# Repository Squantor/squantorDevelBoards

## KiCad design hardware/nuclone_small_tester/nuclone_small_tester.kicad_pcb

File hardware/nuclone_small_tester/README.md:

# Small nuclone peripheral tester
Small nuclone expansion board used for peripheral testing of nuclone boards
## TODO's
Still some things need to be done:
* schematic entry (WIP)
* PCB layout (TODO)
* Review with one night in between (TODO)
* Produce at [OSHPARK](https://oshpark.com/) (TODO)
* Assemble (TODO)
* Test & characterise (TODO)
* update Readme.md with pictures and BOM (TODO)

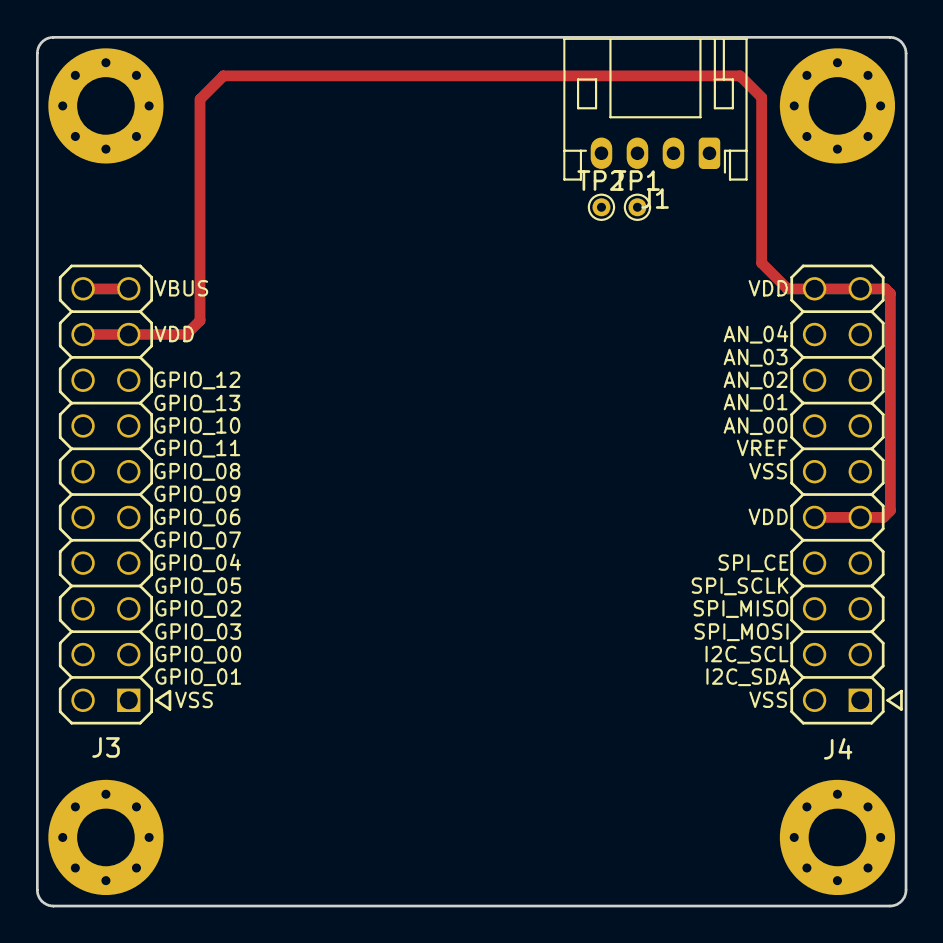
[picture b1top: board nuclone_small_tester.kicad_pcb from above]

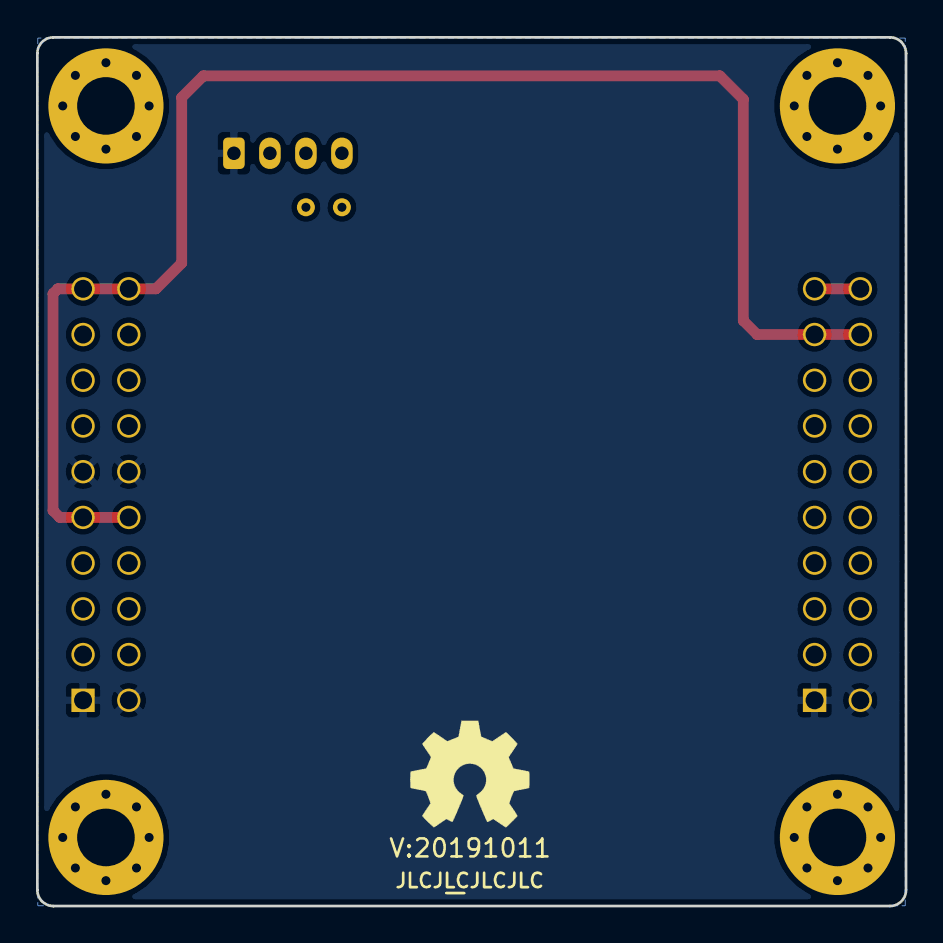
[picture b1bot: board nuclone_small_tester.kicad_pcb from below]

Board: 2 copper layers, 48.3 x 48.3 mm, 12 parts (3 on the bottom side), 5 nets.

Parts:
H1, H2, H3, H4: MountingHole; MountingHole_3.2mm_M3_Pad_Via
J1: DevBoardUartInput; JST_PH_S4B-PH-K_1x04_P2.00mm_Horizontal
J3: nuclone_small_exp_gpio
J4: nuclone_small_exp_bus_analog
N1: OHWLOGO; OSHW-Symbol_6.7x6mm_SilkScreen
N2: 20191011; Label_version
N3: JLCJLCJLCJLC; Label_Generic
TP1, TP2: testpad; TestPoint_THTPad_D1.0mm_Drill0.5mm

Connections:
/UART_RX: J1.3, TP1.1
/UART_TX: J1.4, TP2.1
/VBUS: J1.2, J3.19, J3.20
/VDD: J3.17, J3.18, J4.9, J4.10, J4.19, J4.20
/VSS: J1.1, J3.1, J3.2, J4.1, J4.2, J4.11, J4.12

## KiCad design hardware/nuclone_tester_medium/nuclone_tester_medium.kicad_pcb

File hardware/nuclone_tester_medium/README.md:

# Nuclone tester for medium sized boards
Test jig for the Medium sized nuclone boards.
## TODO's
Still some things need to be done:
* schematic entry (WIP)
* PCB layout (WIP)
* Review with one night in between (TODO)
* Produce at [JLCPCB](https://jlcpcb.com/) (TODO)
* Assemble (TODO)
* Test & characterise (TODO)
* update Readme.md with pictures and BOM (TODO)

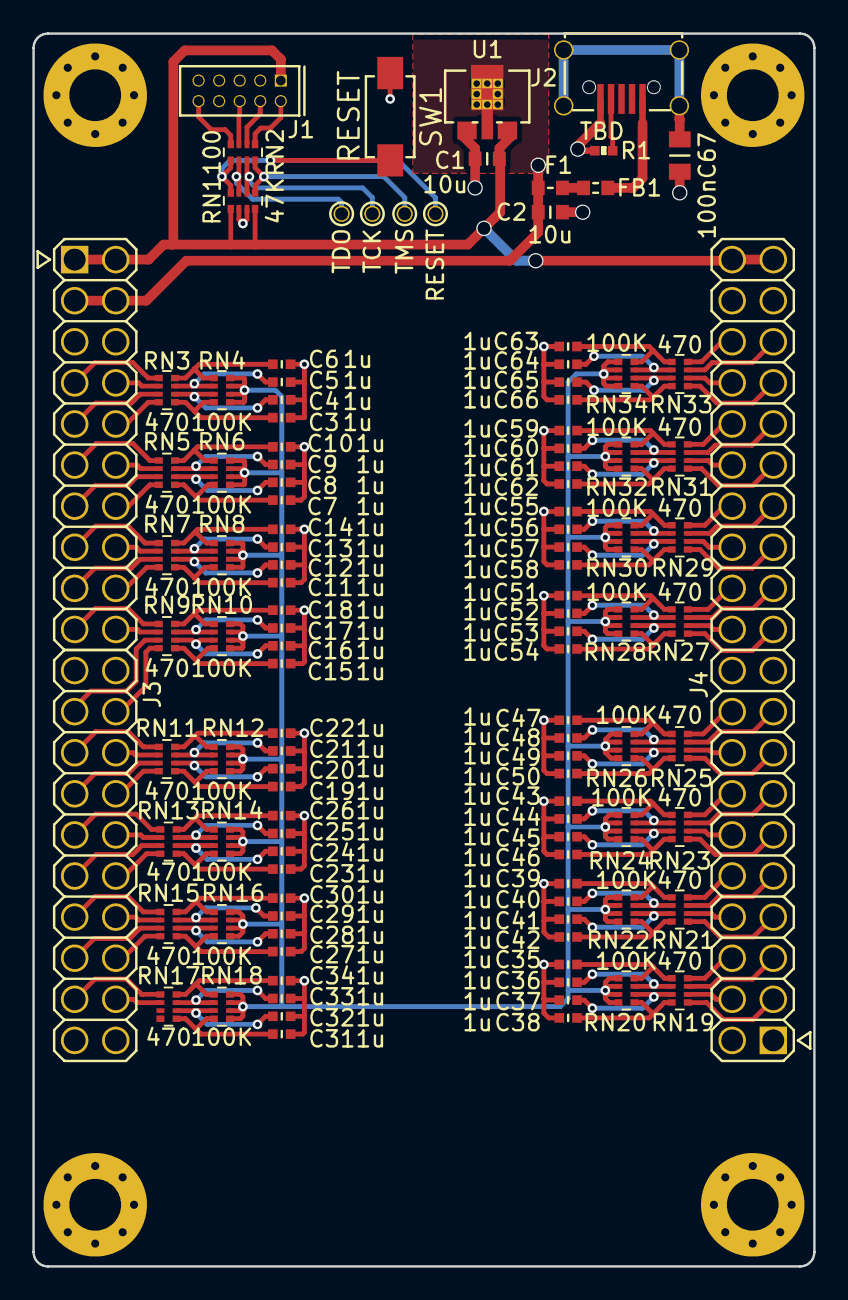
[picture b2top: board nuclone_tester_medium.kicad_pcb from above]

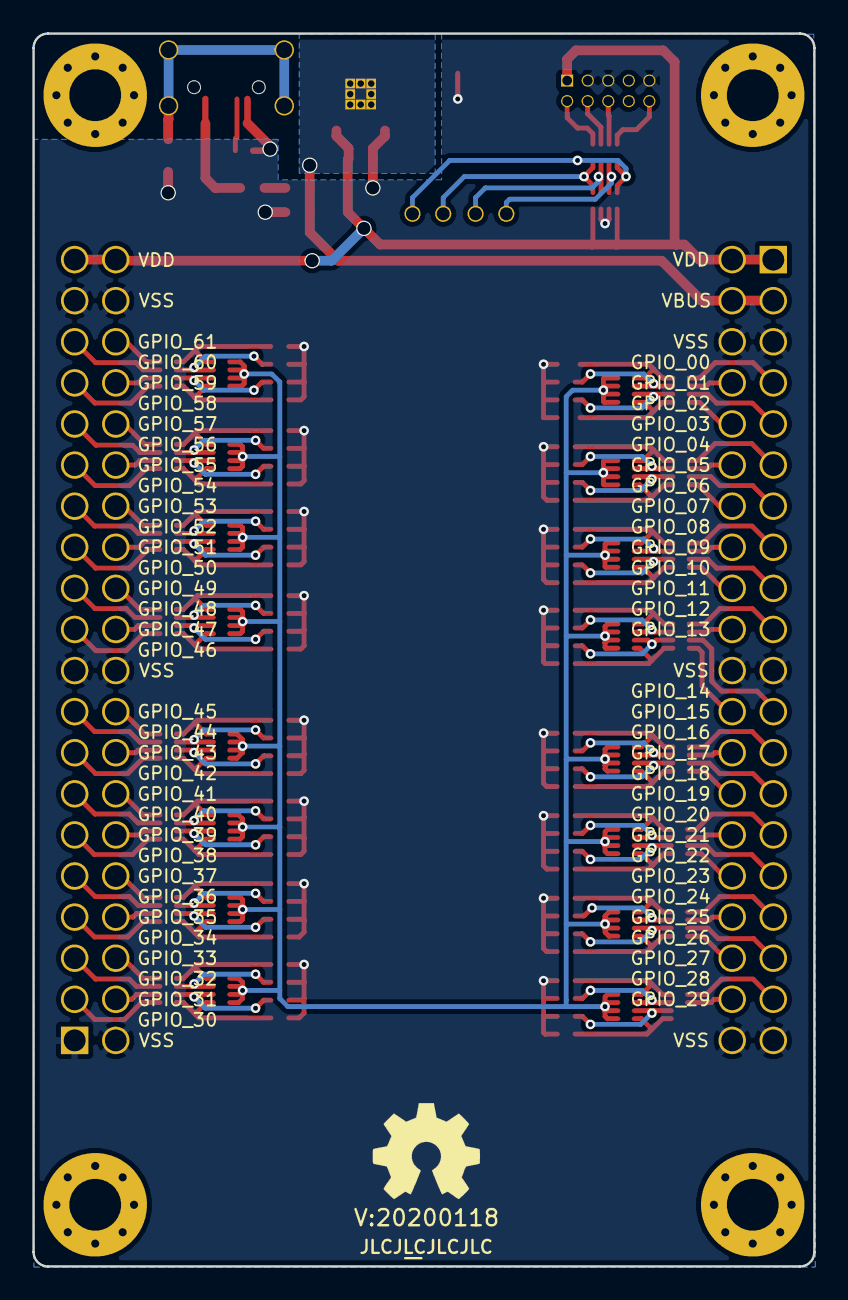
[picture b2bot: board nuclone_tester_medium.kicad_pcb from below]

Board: 2 copper layers, 48.3 x 76.2 mm, 121 parts (3 on the bottom side), 142 nets.

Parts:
C1, C2: 10u; C_0603
C3, C4, C5, C6, C7, C8, C9, C10, C11, C12, C13, C14, C15, C16, C17, C18, C19, C20, C21, C22, C23, C24, C25, C26, C27, C28, C29, C30, C31, C32, C33, C34, C35, C36, C37, C38, C39, C40, C41, C42, C43, C44, C45, C46, C47, C48, C49, C50, C51, C52, C53, C54, C55, C56, C57, C58, C59, C60, C61, C62, C63, C64, C65, C66: 1u; C_0402
C67: 100n; C_0805
F1: 0.5A; F_0603_hand
FB1: 100; L_0603
H1, H2, H3, H4: MountingHole; MountingHole_3.2mm_M3_Pad_Via
J1: JTAG_2X05; Header-0127-2X05-H006
J2: USB-ID; USB-muB-SMD_TH
J3: nuclone_small_left; nuclone_medium_left_1_35mm
J4: nuclone_small_right; nuclone_medium_right_1_35mm
N1: OHWLOGO; OSHW-Symbol_6.7x6mm_SilkScreen
N2: 20200118; Label_version
N3: JLCJLCJLCJLC; Label_Generic
R1: TBD; R_0402_hand
RN1: 47K; R_Array_Convex_4x0402
RN2: 100; R_Array_Convex_4x0402
RN3, RN5, RN7, RN9, RN11, RN13, RN15, RN17, RN19, RN21, RN23, RN25, RN27, RN29, RN31, RN33: 470; R_Array_Convex_4x0402
RN4, RN6, RN8, RN10, RN12, RN14, RN16, RN18, RN20, RN22, RN24, RN26, RN28, RN30, RN32, RN34: 100K; R_Array_Convex_4x0402
SW1: RESET; DTSM3
TP1: TMS; TestPoint_Hole_D0.8mm
TP2: TCK; TestPoint_Hole_D0.8mm
TP3: TDO; TestPoint_Hole_D0.8mm
TP4: RESET; TestPoint_Hole_D0.8mm
U1: MCP1702-MB; SOT89-SOT23-Dual-NXP

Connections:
/GPIO_00: J3.7, RN3.1
/GPIO_01: J3.8, RN3.2
/GPIO_02: J3.9, RN3.3
/GPIO_03: J3.10, RN3.4
/GPIO_04: J3.11, RN5.1
/GPIO_05: J3.12, RN5.2
/GPIO_06: J3.13, RN5.3
/GPIO_07: J3.14, RN5.4
/GPIO_08: J3.15, RN7.1
/GPIO_09: J3.16, RN7.2
/GPIO_10: J3.17, RN7.3
/GPIO_11: J3.18, RN7.4
/GPIO_12: J3.19, RN9.1
/GPIO_13: J3.20, RN9.2
/GPIO_14: J3.23, RN9.3
/GPIO_15: J3.24, RN9.4
/GPIO_16: J3.25, RN11.1
/GPIO_17: J3.26, RN11.2
/GPIO_18: J3.27, RN11.3
/GPIO_19: J3.28, RN11.4
/GPIO_20: J3.29, RN13.1
/GPIO_21: J3.30, RN13.2
/GPIO_22: J3.31, RN13.3
/GPIO_23: J3.32, RN13.4
/GPIO_24: J3.33, RN15.1
/GPIO_25: J3.34, RN15.2
/GPIO_26: J3.35, RN15.3
/GPIO_27: J3.36, RN15.4
/GPIO_28: J3.37, RN17.1
/GPIO_29: J3.38, RN17.2
/GPIO_30: J4.3, RN19.1
/GPIO_31: J4.4, RN19.2
/GPIO_32: J4.5, RN19.3
/GPIO_33: J4.6, RN19.4
/GPIO_34: J4.7, RN21.1
/GPIO_35: J4.8, RN21.2
/GPIO_36: J4.9, RN21.3
/GPIO_37: J4.10, RN21.4
/GPIO_38: J4.11, RN23.1
/GPIO_39: J4.12, RN23.2
/GPIO_40: J4.13, RN23.3
/GPIO_41: J4.14, RN23.4
/GPIO_42: J4.15, RN25.1
/GPIO_43: J4.16, RN25.2
/GPIO_44: J4.17, RN25.3
/GPIO_45: J4.18, RN25.4
/GPIO_46: J4.21, RN27.1
/GPIO_47: J4.22, RN27.2
/GPIO_48: J4.23, RN27.3
/GPIO_49: J4.24, RN27.4
/GPIO_50: J4.25, RN29.1
/GPIO_51: J4.26, RN29.2
/GPIO_52: J4.27, RN29.3
/GPIO_53: J4.28, RN29.4
/GPIO_54: J4.29, RN31.1
/GPIO_55: J4.30, RN31.2
/GPIO_56: J4.31, RN31.3
/GPIO_57: J4.32, RN31.4
/GPIO_58: J4.33, RN33.1
/GPIO_59: J4.34, RN33.2
/GPIO_60: J4.35, RN33.3
/GPIO_61: J4.36, RN33.4
/PIO0_2_MCU: RN1.5, RN2.8, TP1.1
/PIO0_3_MCU: RN1.6, RN2.7, TP2.1
/PIO0_5_MCU: RN1.8, RN2.5, SW1.2, TP4.1
/SWO_TDO: RN1.7, RN2.6, TP3.1
/Stimulus: RN4.5, RN4.6, RN4.7, RN4.8, RN6.5, RN6.6, RN6.7, RN6.8, RN8.5, RN8.6, RN8.7, RN8.8, RN10.5, RN10.6, RN10.7, RN10.8, RN12.5, RN12.6, RN12.7, RN12.8, RN14.5, RN14.6, RN14.7, RN14.8, RN16.5, RN16.6, RN16.7, RN16.8, RN18.5, RN18.6, RN18.7, RN18.8, RN20.5, RN20.6, RN20.7, RN20.8, RN22.5, RN22.6, RN22.7, RN22.8, RN24.5, RN24.6, RN24.7, RN24.8, RN26.5, RN26.6, RN26.7, RN26.8, RN28.5, RN28.6, RN28.7, RN28.8, RN30.5, RN30.6, RN30.7, RN30.8, RN32.5, RN32.6, RN32.7, RN32.8, RN34.5, RN34.6, RN34.7, RN34.8
/VBUS: C2.2, F1.1, J3.3, J3.4, U1.2
/VDD: C1.1, J1.1, J3.1, J3.2, J4.39, J4.40, RN1.1, RN1.4, U1.3
/VSS: C1.2, C2.1, C3.2, C4.2, C5.2, C6.2, C7.2, C8.2, C9.2, C10.2, C11.2, C12.2, C13.2, C14.2, C15.2, C16.2, C17.2, C18.2, C19.2, C20.2, C21.2, C22.2, C23.2, C24.2, C25.2, C26.2, C27.2, C28.2, C29.2, C30.2, C31.2, C32.2, C33.2, C34.2, C35.2, C36.2, C37.2, C38.2, C39.2, C40.2, C41.2, C42.2, C43.2, C44.2, C45.2, C46.2, C47.2, C48.2, C49.2, C50.2, C51.2, C52.2, C53.2, C54.2, C55.2, C56.2, C57.2, C58.2, C59.2, C60.2, C61.2, C62.2, C63.2, C64.2, C65.2, C66.2, C67.2, J1.3, J1.5, J1.9, J2.5, J3.5, J3.6, J3.21, J3.22, J3.39, J3.40, J4.1, J4.2, J4.19, J4.20, J4.37, J4.38, R1.1, RN1.2, RN1.3, SW1.1, U1.1
unnamed: C3.1, RN3.5, RN4.4
unnamed: C4.1, RN3.6, RN4.3
unnamed: C5.1, RN3.7, RN4.2
unnamed: C6.1, RN3.8, RN4.1
unnamed: C7.1, RN5.5, RN6.4
unnamed: C8.1, RN5.6, RN6.3
unnamed: C9.1, RN5.7, RN6.2
unnamed: C10.1, RN5.8, RN6.1
unnamed: C11.1, RN7.5, RN8.4
unnamed: C12.1, RN7.6, RN8.3
unnamed: C13.1, RN7.7, RN8.2
unnamed: C14.1, RN7.8, RN8.1
unnamed: C15.1, RN9.5, RN10.4
unnamed: C16.1, RN9.6, RN10.3
unnamed: C17.1, RN9.7, RN10.2
unnamed: C18.1, RN9.8, RN10.1
unnamed: C19.1, RN11.5, RN12.4
unnamed: C20.1, RN11.6, RN12.3
unnamed: C21.1, RN11.7, RN12.2
unnamed: C22.1, RN11.8, RN12.1
unnamed: C23.1, RN13.5, RN14.4
unnamed: C24.1, RN13.6, RN14.3
unnamed: C25.1, RN13.7, RN14.2
unnamed: C26.1, RN13.8, RN14.1
unnamed: C27.1, RN15.5, RN16.4
unnamed: C28.1, RN15.6, RN16.3
unnamed: C29.1, RN15.7, RN16.2
unnamed: C30.1, RN15.8, RN16.1
unnamed: C31.1, RN17.5, RN18.4
unnamed: C32.1, RN17.6, RN18.3
unnamed: C33.1, RN17.7, RN18.2
unnamed: C34.1, RN17.8, RN18.1
unnamed: C35.1, RN19.5, RN20.4
unnamed: C36.1, RN19.6, RN20.3
unnamed: C37.1, RN19.7, RN20.2
unnamed: C38.1, RN19.8, RN20.1
unnamed: C39.1, RN21.5, RN22.4
unnamed: C40.1, RN21.6, RN22.3
unnamed: C41.1, RN21.7, RN22.2
unnamed: C42.1, RN21.8, RN22.1
unnamed: C43.1, RN23.5, RN24.4
unnamed: C44.1, RN23.6, RN24.3
unnamed: C45.1, RN23.7, RN24.2
unnamed: C46.1, RN23.8, RN24.1
unnamed: C47.1, RN25.5, RN26.4
unnamed: C48.1, RN25.6, RN26.3
unnamed: C49.1, RN25.7, RN26.2
unnamed: C50.1, RN25.8, RN26.1
unnamed: C51.1, RN27.5, RN28.4
unnamed: C52.1, RN27.6, RN28.3
unnamed: C53.1, RN27.7, RN28.2
unnamed: C54.1, RN27.8, RN28.1
unnamed: C55.1, RN29.5, RN30.4
unnamed: C56.1, RN29.6, RN30.3
unnamed: C57.1, RN29.7, RN30.2
unnamed: C58.1, RN29.8, RN30.1
unnamed: C59.1, RN31.5, RN32.4
unnamed: C60.1, RN31.6, RN32.3
unnamed: C61.1, RN31.7, RN32.2
unnamed: C62.1, RN31.8, RN32.1
unnamed: C63.1, RN33.5, RN34.4
unnamed: C64.1, RN33.6, RN34.3
unnamed: C65.1, RN33.7, RN34.2
unnamed: C66.1, RN33.8, RN34.1
unnamed: C67.1, J2.S
unnamed: F1.2, FB1.1
unnamed: FB1.2, J2.1
unnamed: J1.2, RN2.1
unnamed: J1.4, RN2.2
unnamed: J1.6, RN2.3
unnamed: J1.10, RN2.4
unnamed: J2.4, R1.2

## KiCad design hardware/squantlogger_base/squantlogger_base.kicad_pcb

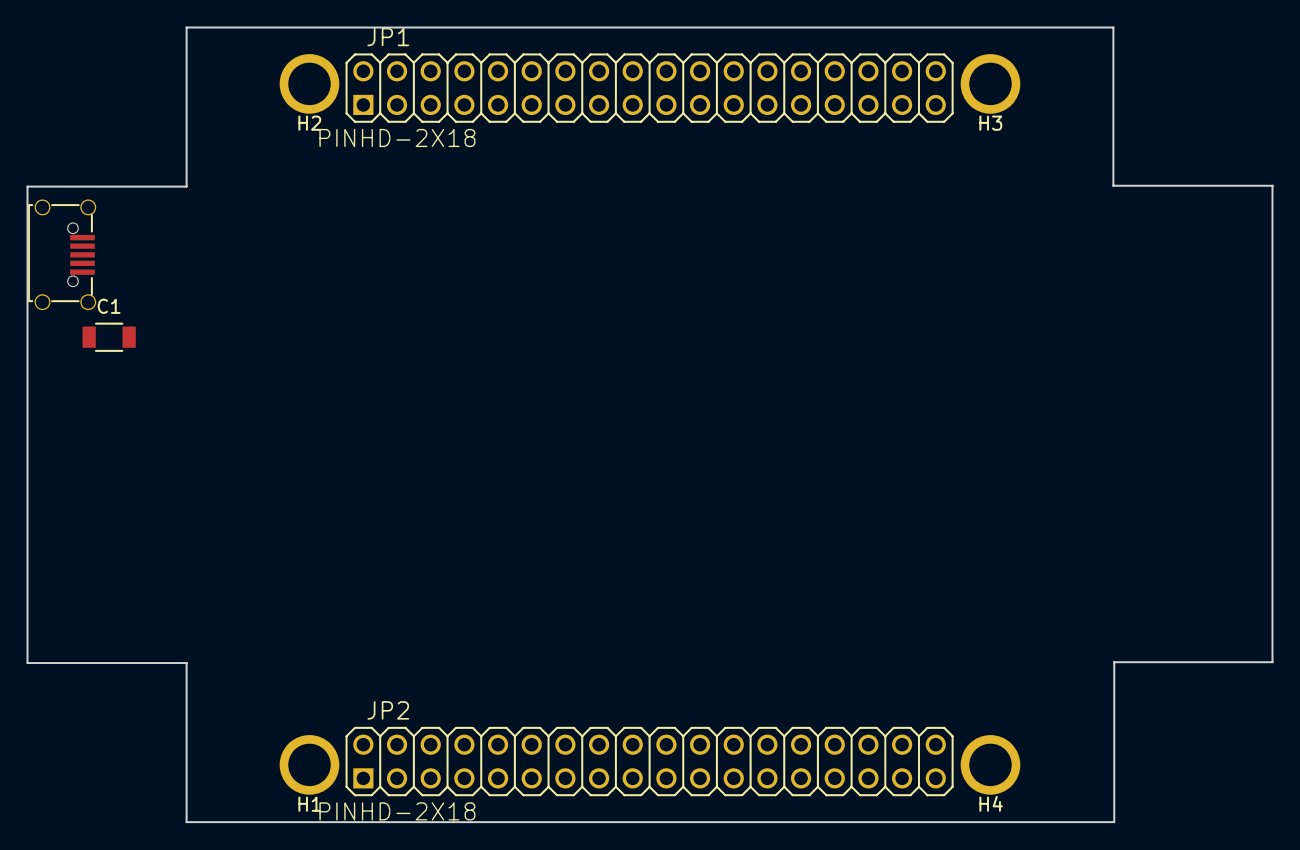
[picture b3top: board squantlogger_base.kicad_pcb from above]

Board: 2 copper layers, 93.9 x 59.9 mm, 8 parts (0 on the bottom side), 2 nets, no tracks yet.

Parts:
C1: 100n; C_1206
H1, H2, H3, H4: Drill_Hole; Drill_Hole_PB1
JP1, JP2: PINHD-2X18; SquantorConnectors-2X18
U1: USB-micro; SquantorUsb-USB-UB-SMD4H

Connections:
Earth: C1.1, H1.S, H2.S, H3.S, H4.S, U1.S
GND: C1.2, U1.5

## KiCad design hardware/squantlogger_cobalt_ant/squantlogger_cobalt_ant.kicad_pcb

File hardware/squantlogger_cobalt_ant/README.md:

# Cobalt Ant datalogger
## TODO
* RTS/CTS have been reversed (did it right with RX and TX)
* SSEL0 not connected to SPI flash CE, its much more useful that way

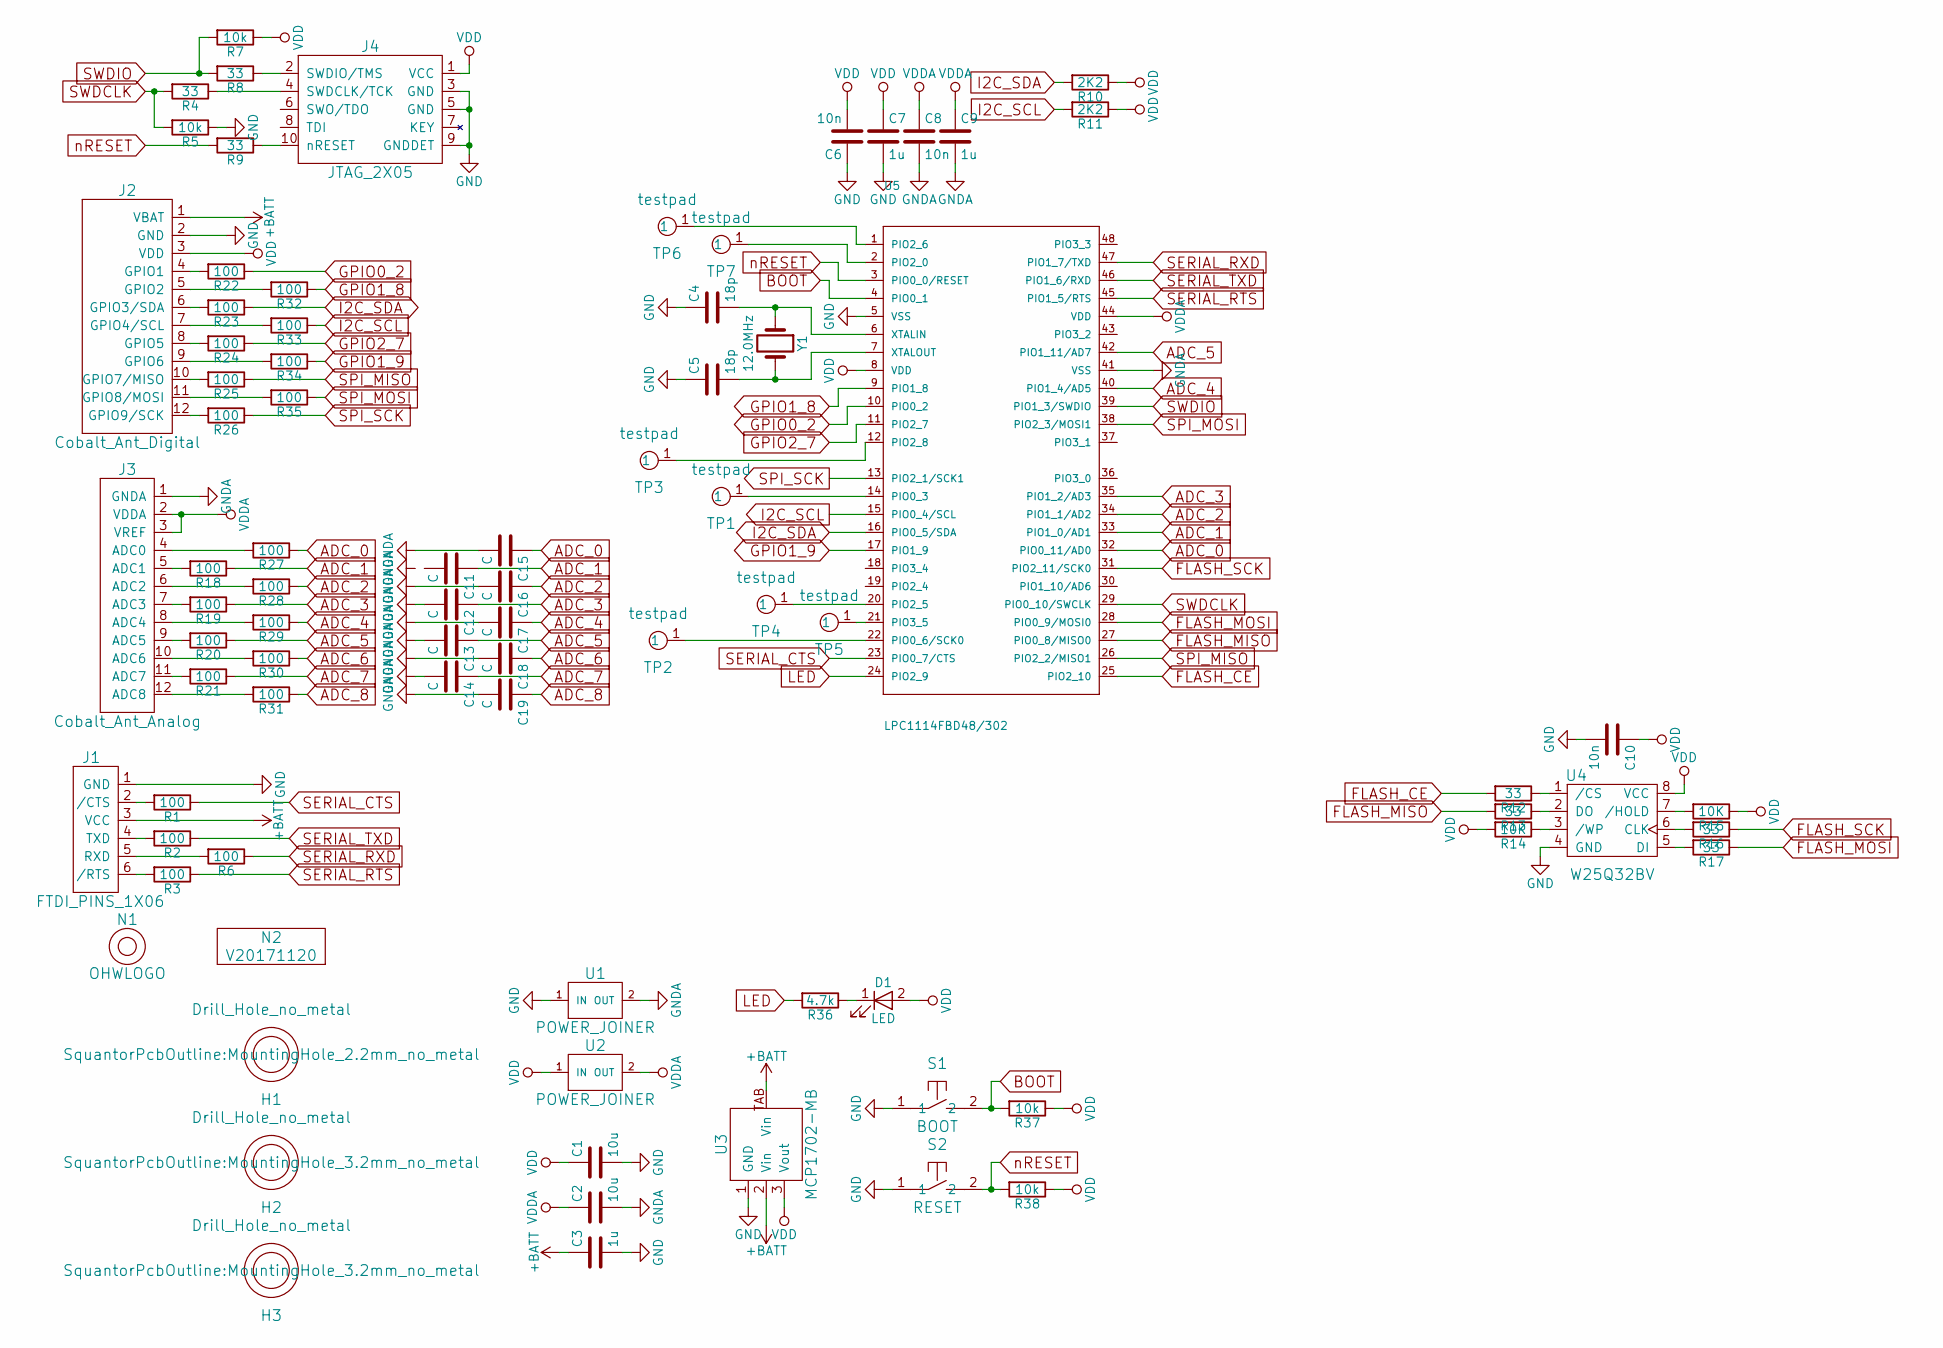
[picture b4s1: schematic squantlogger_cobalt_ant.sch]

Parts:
C1, C2: 10u; C_0805
C3: 1u; C_0805
C4, C5: 18p; C_0402
C6, C8, C10: 10n; C_0402
C7, C9: 1u; C_0402
C11, C12, C13, C14, C15, C16, C17, C18, C19: C; C_0402
D1: LED; R_0603_hand
H1: Drill_Hole_no_metal; MountingHole_2.2mm_no_metal
H2, H3: Drill_Hole_no_metal; MountingHole_3.2mm_no_metal
J1: FTDI_PINS_1X06; Header-0254-1X06-H010
J2: Cobalt_Ant_Digital; Header-0254-1X12-H015
J3: Cobalt_Ant_Analog; Header-0254-1X12-H015
J4: JTAG_2X05; Header-0127-2X05-SMD
N1: OHWLOGO; OSHW-Symbol_8.9x8mm_SilkScreen
N2: V20171120; Label_version
R1, R2, R3, R6, R18, R19, R20, R21, R22, R23, R24, R25, R26, R27, R28, R29, R30, R31, R32, R33, R34, R35: 100; R_0402_hand
R4, R8, R9, R12, R13, R16, R17: 33; R_0402_hand
R5, R7, R37, R38: 10k; R_0402_hand
R10, R11: 2K2; R_0402_hand
R14, R15: 10K; R_0402_hand
R36: 4.7k; R_0402_hand
S1: BOOT; TD-85XU
S2: RESET; TD-85XU
TP1, TP2, TP3, TP4, TP5, TP6, TP7: testpad; TESTPAD_SQ_1MM
U1, U2: POWER_JOINER; R_0402_hand
U3: MCP1702-MB; MB-(SOT-89)
U4: W25Q32BV; WINBOND_SS
U5: LPC1114FBD48/302; SOT313-2
Y1: 12.0MHz; X_5.0_3.2

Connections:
+BATT: C3.1, J1.3 (VCC), J2.1 (VBAT), U3.2 (Vin), U3.TAB (Vin)
ADC_0: C15.1, R27.1, U5.32 (PIO0_11/AD0)
ADC_1: C11.1, R18.1, U5.33 (PIO1_0/AD1)
ADC_2: C16.1, R28.1, U5.34 (PIO1_1/AD2)
ADC_3: C12.1, R19.1, U5.35 (PIO1_2/AD3)
ADC_4: C17.1, R29.1, U5.40 (PIO1_4/AD5)
ADC_5: C13.1, R20.1, U5.42 (PIO1_11/AD7)
ADC_6: C18.1, R30.1
ADC_7: C14.1, R21.1
ADC_8: C19.1, R31.1
BOOT: R37.2, S1.2, U5.4 (PIO0_1)
FLASH_CE: R12.2, U5.25 (PIO2_10)
FLASH_MISO: R13.2, U5.27 (PIO0_8/MISO0)
FLASH_MOSI: R17.1, U5.28 (PIO0_9/MOSI0)
FLASH_SCK: R16.1, U5.31 (PIO2_11/SCK0)
GND: C1.2, C3.2, C4.1, C5.1, C6.1, C7.2, C10.2, J1.1 (GND), J2.2 (GND), J4.3 (GND), J4.5 (GND), J4.9 (GNDDET), R5.1, S1.1, S2.1, U1.1 (IN), U3.1 (GND), U4.4 (GND), U5.5 (VSS)
GNDA: C2.2, C8.2, C9.2, C12.2, C13.2, C14.2, C15.2, C16.2, C17.2, C18.2, C19.2, J3.1 (GNDA), U1.2 (OUT), U5.41 (VSS)
GPIO0_2: R22.1, U5.10 (PIO0_2)
GPIO1_8: R32.1, U5.9 (PIO1_8)
GPIO1_9: R34.1, U5.17 (PIO1_9)
GPIO2_7: R24.1, U5.11 (PIO2_7)
I2C_SCL: R11.2, R33.1, U5.15 (PIO0_4/SCL)
I2C_SDA: R10.2, R23.1, U5.16 (PIO0_5/SDA)
LED: R36.2, U5.24 (PIO2_9)
unnamed: C4.2, U5.6 (XTALIN), Y1.1
unnamed: C5.2, U5.7 (XTALOUT), Y1.2
unnamed: D1.1 (K), R36.1
unnamed: J1.2 (/CTS), R1.2
unnamed: J1.4 (TXD), R2.2
unnamed: J1.5 (RXD), R6.2
unnamed: J1.6 (/RTS), R3.2
unnamed: J2.4 (GPIO1), R22.2
unnamed: J2.5 (GPIO2), R32.2
unnamed: J2.6 (GPIO3/SDA), R23.2
unnamed: J2.7 (GPIO4/SCL), R33.2
unnamed: J2.8 (GPIO5), R24.2
unnamed: J2.9 (GPIO6), R34.2
unnamed: J2.10 (GPIO7/MISO), R25.2
unnamed: J2.11 (GPIO8/MOSI), R35.2
unnamed: J2.12 (GPIO9/SCK), R26.2
unnamed: J3.4 (ADC0), R27.2
unnamed: J3.5 (ADC1), R18.2
unnamed: J3.6 (ADC2), R28.2
unnamed: J3.7 (ADC3), R19.2
unnamed: J3.8 (ADC4), R29.2
unnamed: J3.9 (ADC5), R20.2
unnamed: J3.10 (ADC6), R30.2
unnamed: J3.11 (ADC7), R21.2
unnamed: J3.12 (ADC8), R31.2
unnamed: J4.2 (SWDIO/TMS), R8.1
unnamed: J4.4 (SWDCLK/TCK), R4.1
unnamed: J4.10 (nRESET), R9.1
unnamed: R12.1, U4.1 (/CS)
unnamed: R13.1, U4.2 (DO)
unnamed: R14.1, U4.3 (/WP)
unnamed: R15.2, U4.7 (/HOLD)
unnamed: R16.2, U4.6 (CLK)
unnamed: R17.2, U4.5 (DI)
unnamed: TP1.1, U5.14 (PIO0_3)
unnamed: TP2.1, U5.22 (PIO0_6/SCK0)
unnamed: TP3.1, U5.12 (PIO2_8)
unnamed: TP4.1, U5.20 (PIO2_5)
unnamed: TP5.1, U5.21 (PIO3_5)
unnamed: TP6.1, U5.1 (PIO2_6)
unnamed: TP7.1, U5.2 (PIO2_0)
SERIAL_CTS: R1.1, U5.23 (PIO0_7/CTS)
SERIAL_RTS: R3.1, U5.45 (PIO1_5/RTS)
SERIAL_RXD: R6.1, U5.47 (PIO1_7/TXD)
SERIAL_TXD: R2.1, U5.46 (PIO1_6/RXD)
SPI_MISO: R25.1, U5.26 (PIO2_2/MISO1)
SPI_MOSI: R35.1, U5.38 (PIO2_3/MOSI1)
SPI_SCK: R26.1, U5.13 (PIO2_1/SCK1)
SWDCLK: R4.2, R5.2, U5.29 (PIO0_10/SWCLK)
SWDIO: R7.2, R8.2, U5.39 (PIO1_3/SWDIO)
VDD: C1.1, C6.2, C7.1, C10.1, D1.2 (A), J2.3 (VDD), J4.1 (VCC), R7.1, R10.1, R11.1, R14.2, R15.1, R37.1, R38.1, U2.1 (IN), U3.3 (Vout), U4.8 (VCC), U5.8 (VDD)
VDDA: C2.1, C8.1, C9.1, J3.2 (VDDA), J3.3 (VREF), U2.2 (OUT), U5.44 (VDD)
nRESET: R9.2, R38.2, S2.2, U5.3 (PIO0_0/RESET)

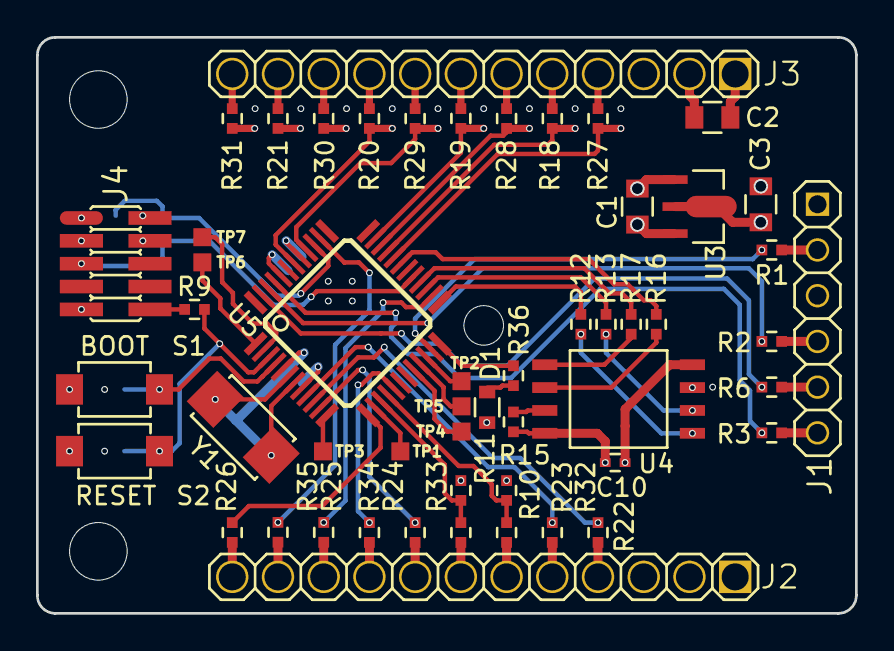
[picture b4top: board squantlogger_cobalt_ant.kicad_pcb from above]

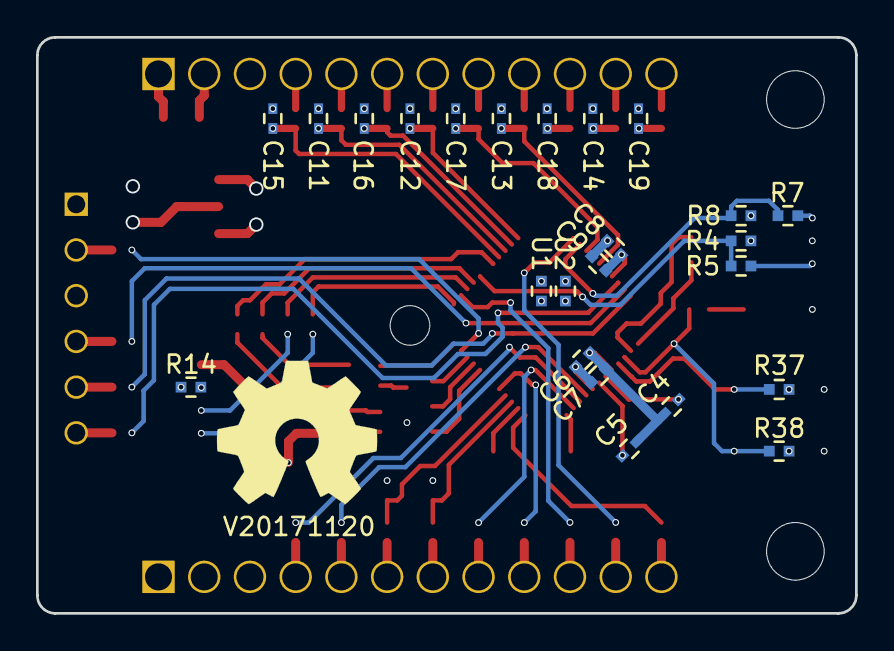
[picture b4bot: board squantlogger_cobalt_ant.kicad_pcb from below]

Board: 4 copper layers, 45.5 x 32.0 mm, 82 parts (26 on the bottom side), 77 nets.

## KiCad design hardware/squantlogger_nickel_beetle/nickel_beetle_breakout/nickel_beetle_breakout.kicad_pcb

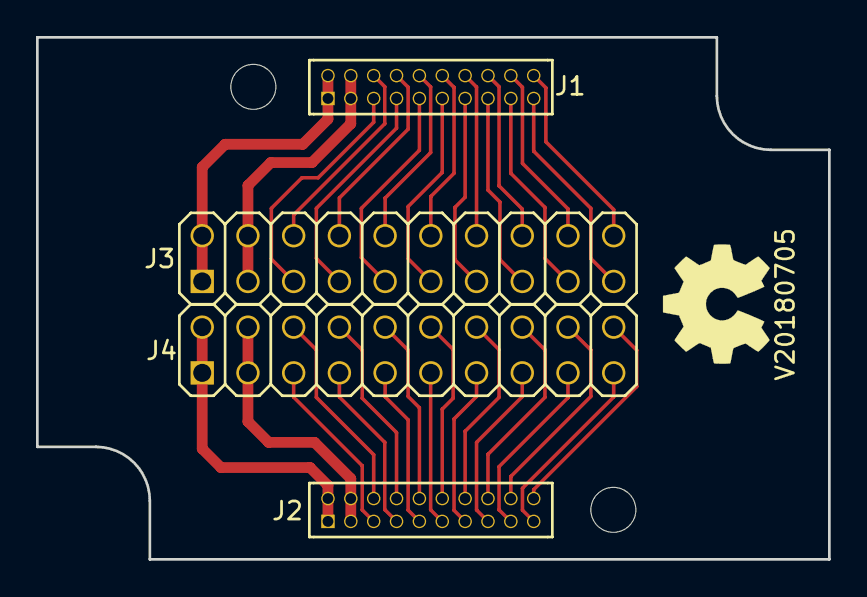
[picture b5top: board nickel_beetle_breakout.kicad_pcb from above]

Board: 2 copper layers, 44.0 x 29.0 mm, 8 parts (0 on the bottom side), 36 nets.

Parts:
H1, H2: Drill_Hole_no_metal; MountingHole_2.5mm_no_metal
J1, J2: Conn_02x10_Odd_Even; Header-0127-2X10-H006
J3, J4: Conn_02x10_Odd_Even; Header-0245-2X10-H010
N1: OHWLOGO; OSHW-Symbol_6.7x6mm_SilkScreen
N2: V20180705; Label_version

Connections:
/ANALOG_00: J1.5, J3.5
/ANALOG_01: J1.6, J3.6
/ANALOG_02: J1.7, J3.7
/ANALOG_03: J1.8, J3.8
/ANALOG_04: J1.9, J3.9
/ANALOG_05: J1.10, J3.10
/ANALOG_06: J1.11, J3.11
/ANALOG_07: J1.12, J3.12
/ANALOG_08: J1.13, J3.13
/ANALOG_09: J1.14, J3.14
/ANALOG_10: J1.15, J3.15
/ANALOG_11: J1.16, J3.16
/ANALOG_12: J1.17, J3.17
/ANALOG_13: J1.18, J3.18
/ANALOG_14: J1.19, J3.19
/ANALOG_15: J1.20, J3.20
/DIGITAL_00: J2.5, J4.5
/DIGITAL_01: J2.6, J4.6
/DIGITAL_02: J2.7, J4.7
/DIGITAL_03: J2.8, J4.8
/DIGITAL_04: J2.9, J4.9
/DIGITAL_05: J2.10, J4.10
/DIGITAL_06: J2.11, J4.11
/DIGITAL_07: J2.12, J4.12
/DIGITAL_08: J2.13, J4.13
/DIGITAL_09: J2.14, J4.14
/DIGITAL_10: J2.15, J4.15
/DIGITAL_11: J2.16, J4.16
/DIGITAL_12: J2.17, J4.17
/DIGITAL_13: J2.18, J4.18
/DIGITAL_14: J2.19, J4.19
/DIGITAL_15: J2.20, J4.20
VDD: J2.1, J2.2, J4.1, J4.2
VDDA: J1.1, J1.2, J3.1, J3.2
VSS: J2.3, J2.4, J4.3, J4.4
VSSA: J1.3, J1.4, J3.3, J3.4

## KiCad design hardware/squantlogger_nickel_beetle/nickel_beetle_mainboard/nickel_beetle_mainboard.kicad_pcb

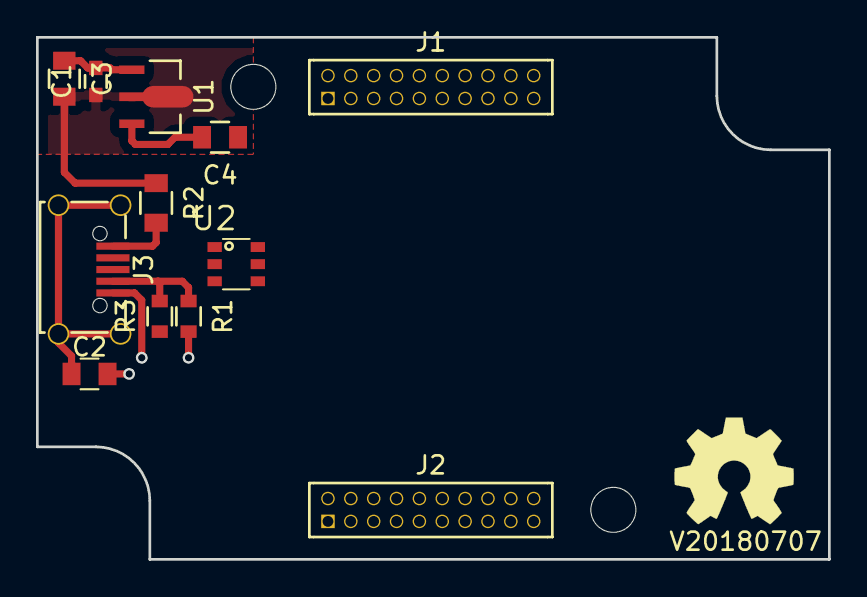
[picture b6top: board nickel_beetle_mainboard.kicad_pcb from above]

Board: 4 copper layers, 44.0 x 29.0 mm, 16 parts (0 on the bottom side), 10 nets.

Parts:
C1: 100n; C_0603
C2: 100nF; C_0805
C3, C4: 10u; C_0805
H1, H2: Drill_Hole_no_metal; MountingHole_2.5mm_no_metal
J1, J2: Conn_02x10_Odd_Even; Header-0127-2X10-H006
J3: USB-ID; USB-muB-SMD_TH
N1: OHWLOGO; OSHW-Symbol_6.7x6mm_SilkScreen
N2: V20180707; Label_version
R1, R3: R; R_0603_hand
R2: FB; R_0805_hand
U1: MCP1702-MB; MB-(SOT-89)
U2: USBLC6-2; SOT457-SOT23_6

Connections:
+5V: C1.1, C3.2, R2.1, R3.1, U1.2, U1.TAB, U2.5
unnamed: C2.1, J3.S
unnamed: J3.1, R2.2
unnamed: J3.2, U2.1
unnamed: J3.3, U2.3
unnamed: J3.4, R1.1, R3.2
VDD: C4.2, J2.1, J2.2, U1.3
VDDA: J1.1, J1.2
VSS: C1.2, C2.2, C3.1, C4.1, J2.3, J2.4, J3.5, R1.2, U1.1, U2.2
VSSA: J1.3, J1.4
